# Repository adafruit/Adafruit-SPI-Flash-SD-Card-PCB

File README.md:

## Adafruit SPI Flash SD Card PCB

<a href="http://www.adafruit.com/products/4899"><br/>
Click here to purchase one from the Adafruit shop</a>

PCB files for the Adafruit SPI Flash SD Card.

Format is EagleCAD schematic and board layout
* https://www.adafruit.com/product/4899

### Description

This breakout is for a fascinating chip - it looks like an SPI Flash storage chip (like the GD25Q16) but its really an SD card, in an SMT chip format. What that means is that you wire up like an SD card breakout, and use the SD card libraries you already have for your microcontroller. For example, you can use the built in SD library in Arduino, or for CircuitPython we have an sdcard library. The breakout will act just like a 512 MB sized card with FAT formatting (it's pre-formatted).

You might be wondering why you'd want such a thing - after all you can't plug it into a computer to get the files off like MicroSD cards. For some use cases, such as data logging in a high-vibration device where you don't want the SD card to come loose, or for when you need to reduce size, or when the microcontroller provides a USB mass storage interface, this chip could very useful.

Compared to plain SPI flash, this NAND memory chip handles all the wear leveling and ECC calculation. You don't have to manually erase blocks, you just write and read them like you would with any SD card.You can clock it up 50 MHz and the 'write speed class' is 8 (although you may not be able to get that fast with plain 1-bit SPI compared to SDIO).

We made this breakout to be a quickstart for this chip. We wired the chip in "SPI" mode, with a level shifters so you can use it with 3V or 5V logic easily. You also get a 3.3V regulator and a pullup on CS. Wire up the SPI pins to your microcontroller, use your favorite SD library and you'll be ready to rock in minutes!

### License

Adafruit invests time and resources providing this open source design, please support Adafruit and open-source hardware by purchasing products from [Adafruit](https://www.adafruit.com)!

Designed by Limor Fried/Ladyada for Adafruit Industries.

Creative Commons Attribution/Share-Alike, all text above must be included in any redistribution.
See license.txt for additional details.

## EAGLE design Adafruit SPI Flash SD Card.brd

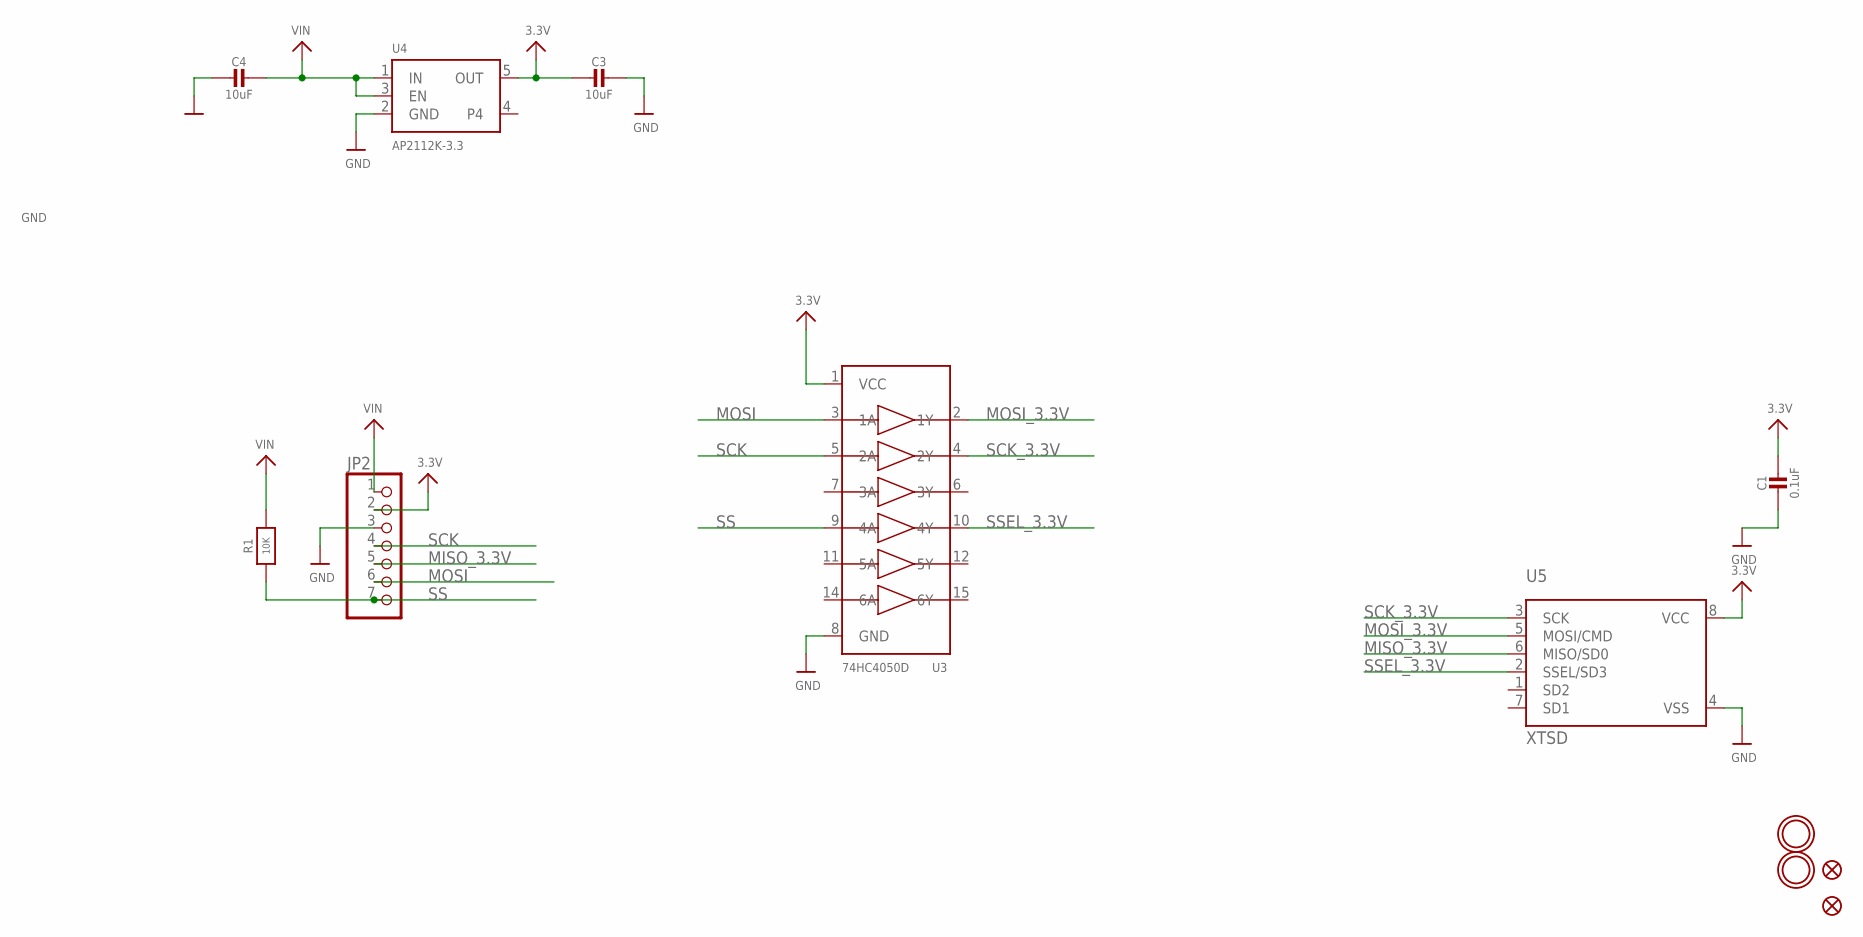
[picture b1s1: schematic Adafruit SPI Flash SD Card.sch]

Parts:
C1: 0.1uF; 0603-NO
C3, C4: 10uF; 0805-NO
FID2, FID3: FIDUCIAL_1MM
JP2: HEADER-1X770MIL; 1X07_ROUND_70
R1: 10K; 0603-NO
U3: 74HC4050D; TSSOP16
U4: AP2112K-3.3; SOT23-5
U5: XTSD; LGA8_8X6
U$16, U$17: MOUNTINGHOLE2.5; MOUNTINGHOLE_2.5_PLATED

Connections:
3.3V: C1.1, C3.2, JP2.2, U3.1 (VCC), U4.5 (OUT), U5.8 (VCC)
GND: C1.2, C3.1, C4.2, JP2.3, U3.8 (GND), U4.2 (GND), U5.4 (VSS)
MISO_3.3V: JP2.5, U5.6 (MISO/SD0)
MOSI: JP2.6, U3.3 (1A)
MOSI_3.3V: U3.2 (1Y), U5.5 (MOSI/CMD)
SCK: JP2.4, U3.5 (2A)
SCK_3.3V: U3.4 (2Y), U5.3 (SCK)
SS: JP2.7, R1.1, U3.9 (4A)
SSEL_3.3V: U3.10 (4Y), U5.2 (SSEL/SD3)
VIN: C4.1, JP2.1, R1.2, U4.1 (IN), U4.3 (EN)

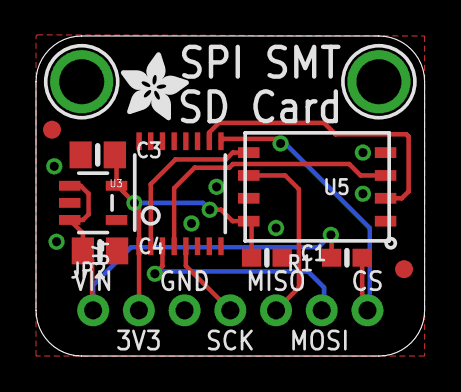
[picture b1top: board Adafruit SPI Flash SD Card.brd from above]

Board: 2 copper layers, 21.6 x 17.8 mm, 14 parts (1 on the bottom side), 10 nets.

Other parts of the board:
U$19: ADAFRUIT_3.5MM
U$21: PCBFEAT-REV-040

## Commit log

2021-01-27 Adding board files.

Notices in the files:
parts and their libraries:
microbuilder: This work is placed in the public domain, and may be freely used for commercial and non-commercial work with the following conditions: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
